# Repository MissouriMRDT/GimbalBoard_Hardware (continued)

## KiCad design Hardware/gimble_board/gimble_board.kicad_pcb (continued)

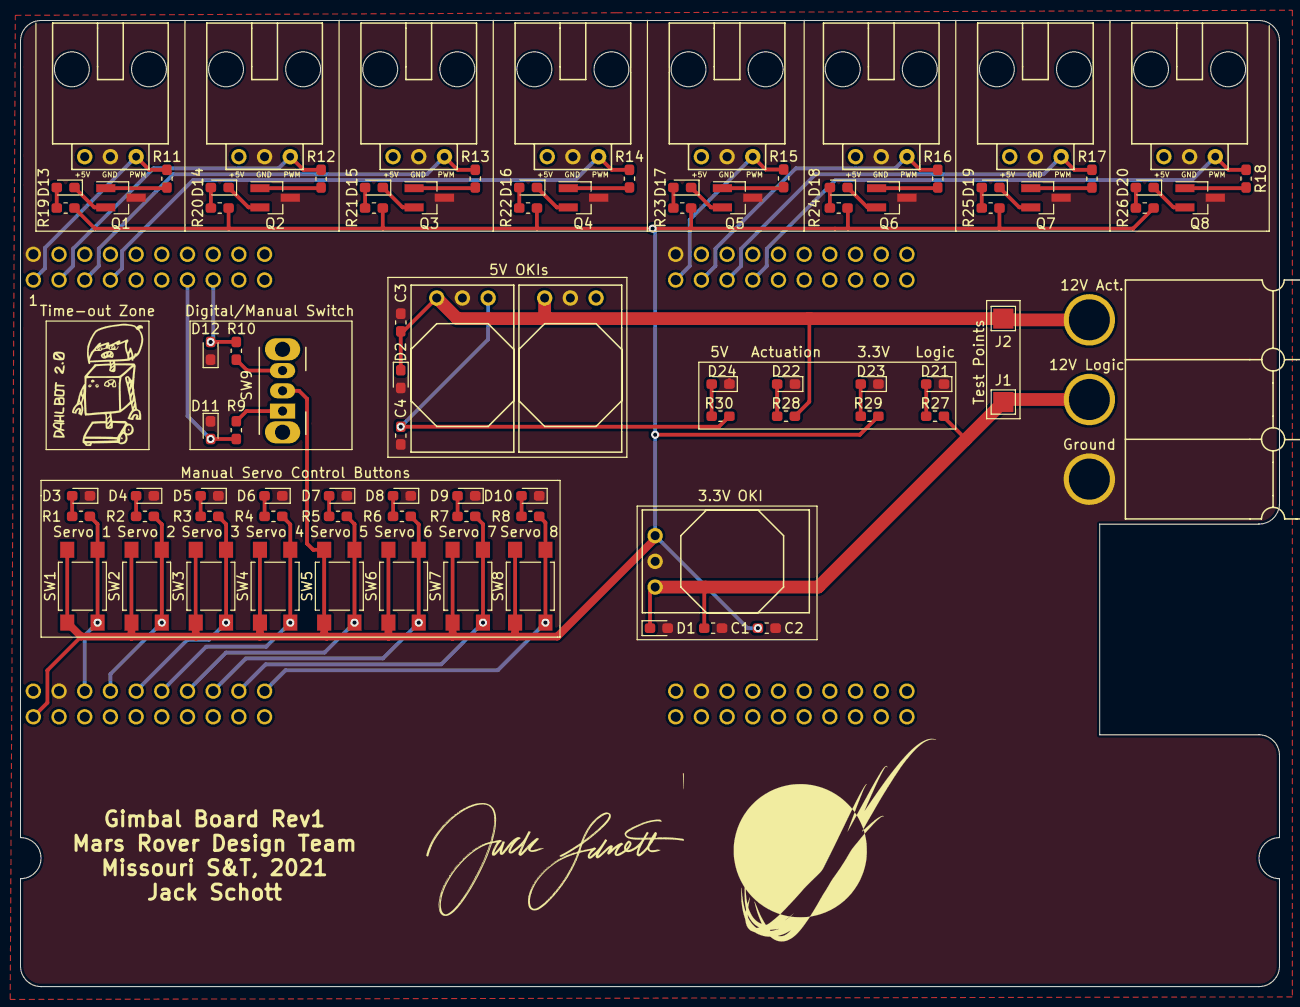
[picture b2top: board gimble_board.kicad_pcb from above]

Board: 2 copper layers, 124.5 x 95.5 mm, 90 parts (0 on the bottom side), 61 nets.

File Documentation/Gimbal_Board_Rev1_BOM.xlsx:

Id | Designator | Package | Quantity | Designation | Item Name | Part Number | Vendor | Cost Per Item | Cost | URL | Comments | Quantity
1 | U1 | TM4C129E_Launchpad_FULL_THT_BOTTOM | 4 | TM4C129E_Launchpad | 20 Position Header Connector Through Hole | S6106-ND | DigiKey | 1.26 |  | https://www.digikey.com/product-detail/en/sullins-connector-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 |  | 4 |  | Total Cost
2 | R6,R5,R26,R25,R24,R23,R22,R21,R20,R19,R18,R17,R1,R2,R3,R4,R28,R7,R8 | R_0603_1608Metric_Pad1.05x0.95mm_HandSolder | 19 | 330 | 330 Ohms ±1% 0.1W, 1/10W Chip Resistor 0603 | P330HCT-ND | DigiKey | 0.1 |  | https://www.digikey.com/product-detail/en/panasonic-electron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 |  | 19 |  | 14.103
3 | R14,R27,R9,R10,R11,R12,R13,R15,R16 | R_0603_1608Metric_Pad1.05x0.95mm_HandSolder | 9 | 500 | SMD Chip Resistor, 0603 [1608 Metric], 510 ohm, CRCW e3 Series, 75 V, Thick Fil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 | 59M6823 | Newark | 0.004 |  | https://www.newark.com/vishay/crcw0603510rjnea/res-thick-fil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 |  | 9
4 | Q6,Q5,Q8,Q7,Q4,Q3,Q2,Q1 | SOT-23_Handsoldering | 8 | Q_NMOS_GDS | N-Channel 60V 310mA (Ta) 370mW (Ta) Surface Mount SOT-23 | DMN65D8L-7DICT-ND | DigiKey | 0.17 |  | https://www.digikey.com/product-detail/en/diodes-incorporate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 |  | 8
5 | D6,D18,D17,D16,D15,D14,D13,D12,D11,D10,D9,D1,D2,D3,D4,D5,D7,D8 | D_0603_1608Metric_Pad1.05x0.95mm_HandSolder | 18 | LED | LED, QuasarBrite, Orange, SMD, 0603, 20 mA, 2 V, 610 nm | 28M9279 | Newark | 0.117 |  | https://www.newark.com/lumex/sml-lx0603sow-tr/led-orange-0-8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 |  | 18
6 | Conn6,Conn1,Conn2,Conn3,Conn4,Conn5,Conn7,Conn8 | MOLEX_SL_03_Horizontal | 8 | Molex_SL_03 | Connector Header Through Hole, Right Angle 3 position 0.100" (2.54mm) | WM4901-ND | DigiKey | 1.02 |  | https://www.digikey.com/products/en?keywords=WM4901-ND |  | 8
7 | SW10 | SW_CuK_OS102011MA1QN1_SPDT_Angled | 1 | SW_SPDT | Slide Switch SPDT Through Hole, Right Angle | CKN9559-ND | DigiKey | 0.38 |  | https://www.digikey.com/products/en?keywords=CKN9559-ND |  | 1
8 | SW9,SW8,SW7,SW6,SW5,SW4,SW3,SW2,SW1 | SW_SPST_TL3305A | 9 | SW_Push | Tactile Switch SPST-NO Top Actuated Surface Mount | EG5350CT-ND | DigiKey | 0.2 |  | https://www.digikey.com/product-detail/en/e-switch/TL3305AF1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 |  | 9
9 | C6,C5,C7 | CP_Radial_D8.0mm_P3.50mm | 3 | 470u | CAP ALUM 470UF 20% 16V RADIAL | 1189-1859-ND | DigiKey | 0.4 |  | https://www.digikey.com/product-detail/en/rubycon/16ZLH470ME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 |  | 3
10 | C1,C2 | C_0603_1608Metric_Pad1.05x0.95mm_HandSolder | 2 | 10 uF | CAP CER 10UF 16V X5R 0603 | 490-12736-1-ND | DigiKey | 0.39 |  | https://www.digikey.com/product-detail/en/murata-electronics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 |  | 2
11 | C3,C4 | C_0603_1608Metric_Pad1.05x0.95mm_HandSolder | 2 | 10uF | CAP CER 10UF 16V X5R 0603 | 490-12736-1-ND | DigiKey | 0.39 |  | https://www.digikey.com/product-detail/en/murata-electronics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 |  | 2
12 | D20 | D_0603_1608Metric_Pad1.05x0.95mm_HandSolder | 1 | 3V_LED | LED, QuasarBrite, Green, SMD, 0603, 20 mA, 2.2 V, 565 nm | 75K1440 | Newark | 0.243 |  | https://www.newark.com/lumex/sml-lx0603gw-tr/led-green-0-8mm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 |  | 1
13 | D19 | D_0603_1608Metric_Pad1.05x0.95mm_HandSolder | 1 | 5V_Act_LED | LED, QuasarBrite, Green, SMD, 0603, 20 mA, 2.2 V, 565 nm | 75K1440 | Newark | 0.243 |  | https://www.newark.com/lumex/sml-lx0603gw-tr/led-green-0-8mm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 |  | 1
14 | U2 | OkI_Horizontal_3V3 | 1 | OKI | Linear Regulator Replacement DC DC Converter 1 Output 3.3V 1.5A 7V - 36V Input | 811-3014-ND | DigiKey | 4.3 |  | https://www.digikey.com/product-detail/en/murata-power-solut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 |  | 1
15 | U3 | OKI_Horizontal_5V | 1 | OKI | Linear Regulator Replacement DC DC Converter 1 Output 5V 1.5A 7V - 36V Input | 811-2692-ND | DigiKey | 4.3 |  | https://www.digikey.com/product-detail/en/murata-power-solut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 |  | 1
16 | Conn9 | Anderson_3_Horizontal_Side_by_Side | 1 | AndersonPP |  |  |  |  |  |  |  | 1
17 | D21 | D_0603_1608Metric_Pad1.05x0.95mm_HandSolder | 1 | 12V_Log_LED | LED, QuasarBrite, Green, SMD, 0603, 20 mA, 2.2 V, 565 nm | 75K1440 | Newark | 0.243 |  | https://www.newark.com/lumex/sml-lx0603gw-tr/led-green-0-8mm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 |  | 1
18 | D22 | D_0603_1608Metric_Pad1.05x0.95mm_HandSolder | 1 | 12V_Act_LED | LED, QuasarBrite, Green, SMD, 0603, 20 mA, 2.2 V, 565 nm | 75K1440 | Newark | 0.243 |  | https://www.newark.com/lumex/sml-lx0603gw-tr/led-green-0-8mm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 |  | 1
19 | R29,R30 | R_0603_1608Metric_Pad1.05x0.95mm_HandSolder | 2 | 1000 | 1 kOhms ±5% 0.25W, 1/4W Chip Resistor 0603 (1608 Metric) Automotive AEC-Q200, P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 | RHM1.0KDCT-ND | DigiKey | 0.1 |  | https://www.digikey.com/product-detail/en/rohm-semiconductor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 |  | 2

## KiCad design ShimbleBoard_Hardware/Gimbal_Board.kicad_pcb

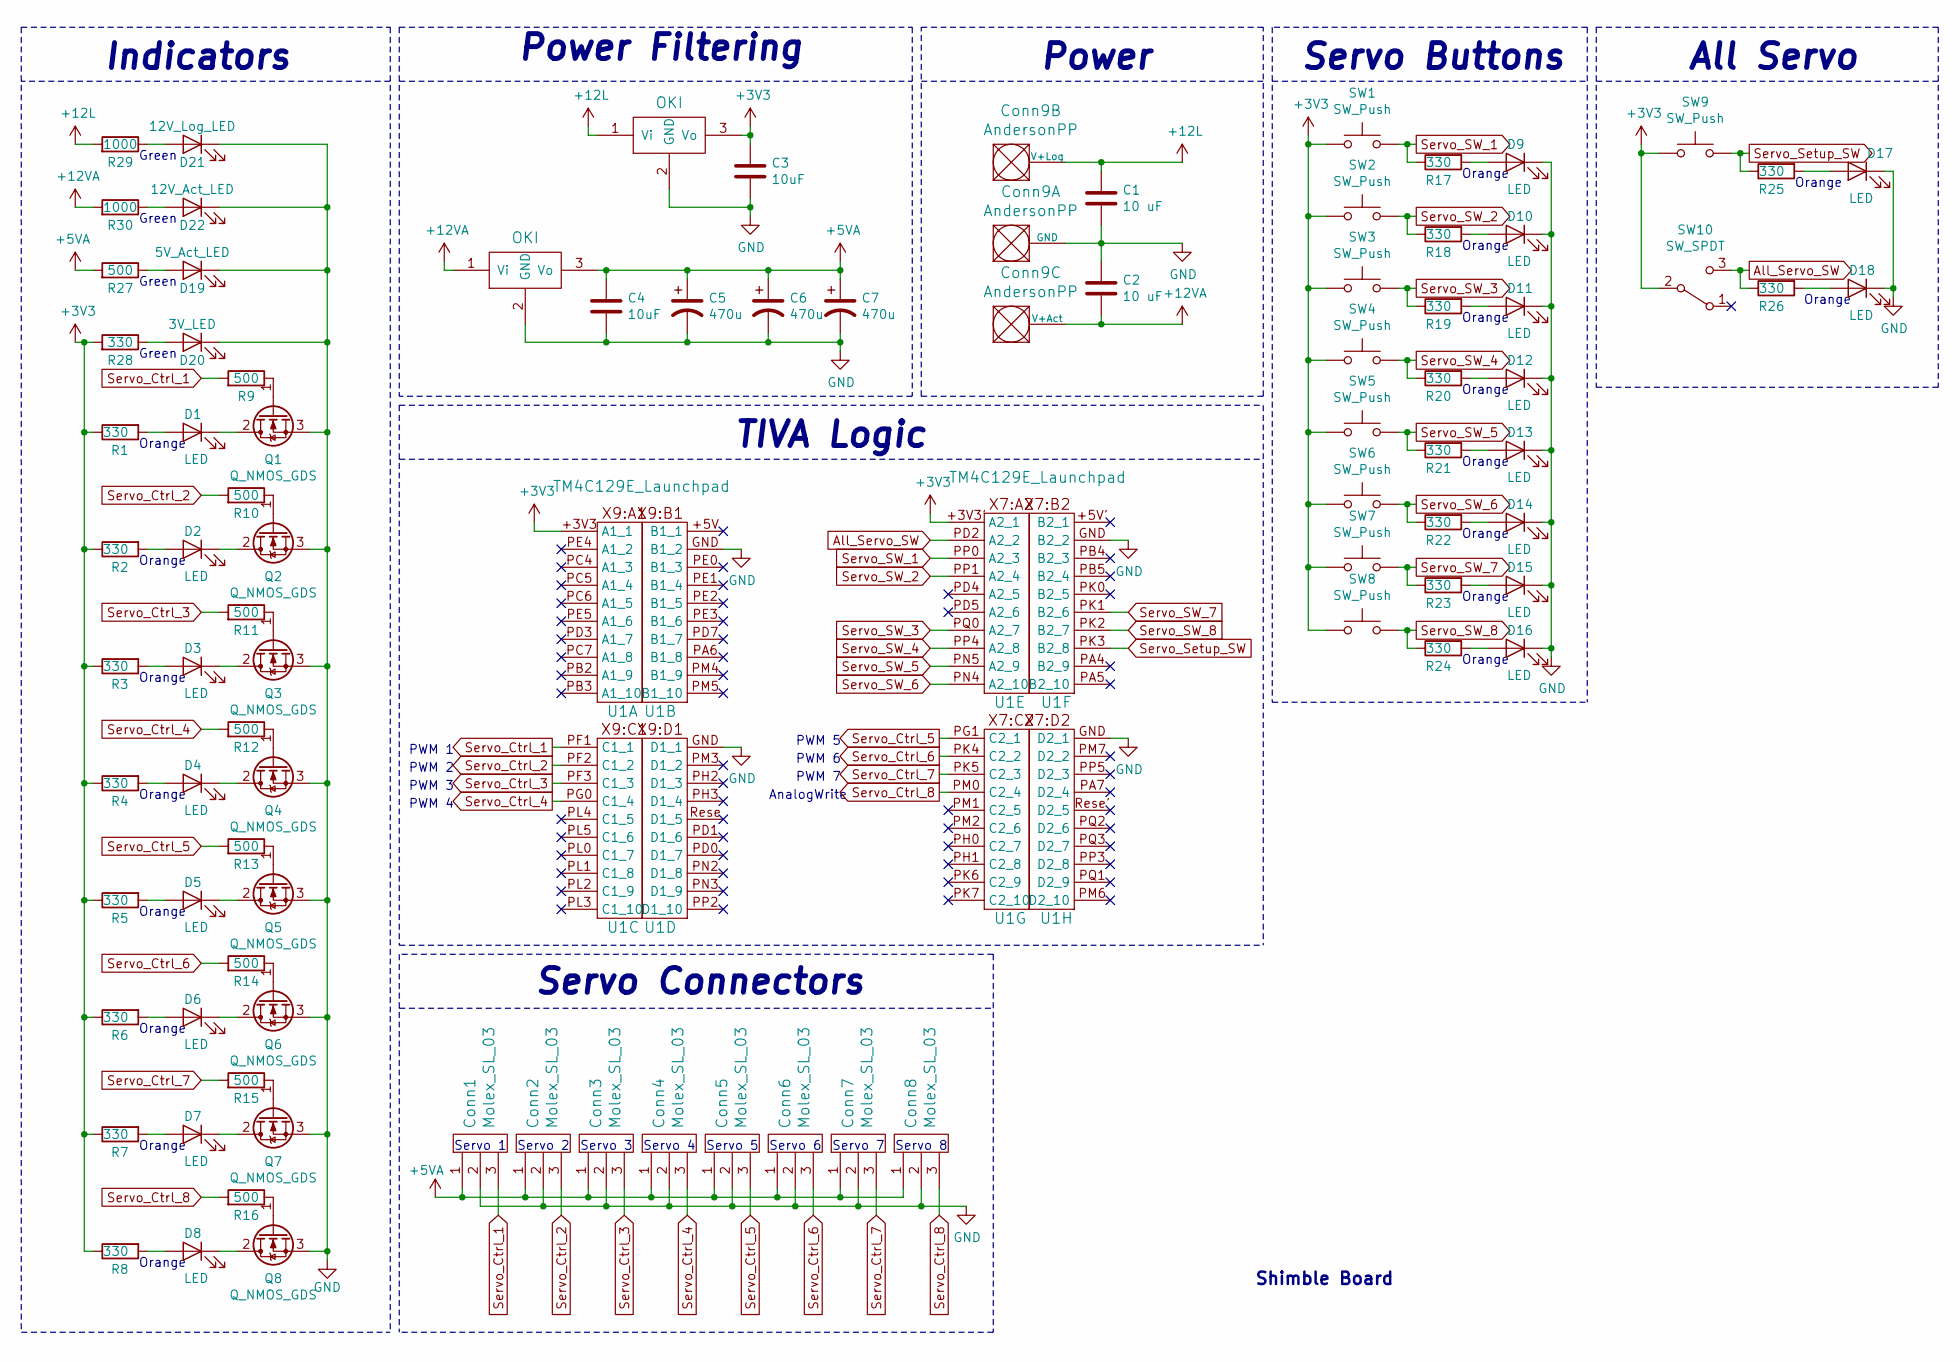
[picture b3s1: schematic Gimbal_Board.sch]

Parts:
C1, C2: 10 uF; C_0603_1608Metric_Pad1.05x0.95mm_HandSolder
C3, C4: 10uF; C_0603_1608Metric_Pad1.05x0.95mm_HandSolder
C5, C6, C7: 470u; CP_Radial_D8.0mm_P3.50mm
Conn1, Conn2, Conn3, Conn4, Conn5, Conn6, Conn7, Conn8: Molex_SL_03; MOLEX_SL_03_Horizontal
Conn9: AndersonPP; Anderson_3_Horizontal_Side_by_Side
D1, D2, D3, D4, D5, D6, D7, D8, D9, D10, D11, D12, D13, D14, D15, D16, D17, D18: LED; D_0603_1608Metric_Pad1.05x0.95mm_HandSolder
D19: 5V_Act_LED; D_0603_1608Metric_Pad1.05x0.95mm_HandSolder
D20: 3V_LED; D_0603_1608Metric_Pad1.05x0.95mm_HandSolder
D21: 12V_Log_LED; D_0603_1608Metric_Pad1.05x0.95mm_HandSolder
D22: 12V_Act_LED; D_0603_1608Metric_Pad1.05x0.95mm_HandSolder
Q1, Q2, Q3, Q4, Q5, Q6, Q7, Q8: Q_NMOS_GDS; SOT-23_Handsoldering
R1, R2, R3, R4, R5, R6, R7, R8, R17, R18, R19, R20, R21, R22, R23, R24, R25, R26, R28: 330; R_0603_1608Metric_Pad1.05x0.95mm_HandSolder
R9, R10, R11, R12, R13, R14, R15, R16, R27: 500; R_0603_1608Metric_Pad1.05x0.95mm_HandSolder
R29, R30: 1000; R_0603_1608Metric_Pad1.05x0.95mm_HandSolder
SW1, SW2, SW3, SW4, SW5, SW6, SW7, SW8, SW9: SW_Push; SW_SPST_TL3305A
SW10: SW_SPDT; SW_CuK_OS102011MA1QN1_SPDT_Angled
U1: TM4C129E_Launchpad; TM4C129E_Launchpad_FULL_THT_BOTTOM
U2, U3: OKI; OKI_Horizontal

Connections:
+3V3: C3.1, R1.1, R2.1, R3.1, R4.1, R5.1, R6.1, R7.1, R8.1, R28.2, SW1.1, SW2.1, SW3.1, SW4.1, SW5.1, SW6.1, SW7.1, SW8.1, SW9.1, SW10.2 (B), U1.+3V3 (A1_1), U1.+3V3' (A2_1), U2.3 (Vo)
+5VA: C4.1, C5.1, C6.1, C7.1, Conn1.1, Conn2.1, Conn3.1, Conn4.1, Conn5.1, Conn6.1, Conn7.1, Conn8.1, R27.2, U3.3 (Vo)
+12L: C1.1, Conn9.2 (V+Log), R29.2, U2.1 (Vi)
+12VA: C2.2, Conn9.3 (V+Act), R30.2, U3.1 (Vi)
All_Servo_SW: R26.1, SW10.3 (C), U1.PD2 (A2_2)
GND: C1.2, C2.1, C3.2, C4.2, C5.2, C6.2, C7.2, Conn1.2, Conn2.2, Conn3.2, Conn4.2, Conn5.2, Conn6.2, Conn7.2, Conn8.2, Conn9.1 (GND), D9.1 (K), D10.1 (K), D11.1 (K), D12.1 (K), D13.1 (K), D14.1 (K), D15.1 (K), D16.1 (K), D17.1 (K), D18.1 (K), D19.1 (K), D20.1 (K), D21.1 (K), D22.1 (K), Q1.3 (S), Q2.3 (S), Q3.3 (S), Q4.3 (S), Q5.3 (S), Q6.3 (S), Q7.3 (S), Q8.3 (S), U1.GND (B1_2), U2.2 (GND), U3.2 (GND)
unnamed: D1.1 (K), Q1.2 (D)
unnamed: D1.2 (A), R1.2
unnamed: D2.1 (K), Q2.2 (D)
unnamed: D2.2 (A), R2.2
unnamed: D3.1 (K), Q3.2 (D)
unnamed: D3.2 (A), R3.2
unnamed: D4.1 (K), Q4.2 (D)
unnamed: D4.2 (A), R4.2
unnamed: D5.1 (K), Q5.2 (D)
unnamed: D5.2 (A), R5.2
unnamed: D6.1 (K), Q6.2 (D)
unnamed: D6.2 (A), R6.2
unnamed: D7.1 (K), Q7.2 (D)
unnamed: D7.2 (A), R7.2
unnamed: D8.1 (K), Q8.2 (D)
unnamed: D8.2 (A), R8.2
unnamed: D9.2 (A), R17.2
unnamed: D10.2 (A), R18.2
unnamed: D11.2 (A), R19.2
unnamed: D12.2 (A), R20.2
unnamed: D13.2 (A), R21.2
unnamed: D14.2 (A), R22.2
unnamed: D15.2 (A), R23.2
unnamed: D16.2 (A), R24.2
unnamed: D17.2 (A), R25.2
unnamed: D18.2 (A), R26.2
unnamed: D19.2 (A), R27.1
unnamed: D20.2 (A), R28.1
unnamed: D21.2 (A), R29.1
unnamed: D22.2 (A), R30.1
unnamed: Q1.1 (G), R9.1
unnamed: Q2.1 (G), R10.1
unnamed: Q3.1 (G), R11.1
unnamed: Q4.1 (G), R12.1
unnamed: Q5.1 (G), R13.1
unnamed: Q6.1 (G), R14.1
unnamed: Q7.1 (G), R15.1
unnamed: Q8.1 (G), R16.1
Servo_Ctrl_1: Conn1.3, R9.2, U1.PF1 (C1_1)
Servo_Ctrl_2: Conn2.3, R10.2, U1.PF2 (C1_2)
Servo_Ctrl_3: Conn3.3, R11.2, U1.PF3 (C1_3)
Servo_Ctrl_4: Conn4.3, R12.2, U1.PG0 (C1_4)
Servo_Ctrl_5: Conn5.3, R13.2, U1.PG1 (C2_1)
Servo_Ctrl_6: Conn6.3, R14.2, U1.PK4 (C2_2)
Servo_Ctrl_7: Conn7.3, R15.2, U1.PK5 (C2_3)
Servo_Ctrl_8: Conn8.3, R16.2, U1.PM0 (C2_4)
Servo_SW_1: R17.1, SW1.2, U1.PP0 (A2_3)
Servo_SW_2: R18.1, SW2.2, U1.PP1 (A2_4)
Servo_SW_3: R19.1, SW3.2, U1.PQ0 (A2_7)
Servo_SW_4: R20.1, SW4.2, U1.PP4 (A2_8)
Servo_SW_5: R21.1, SW5.2, U1.PN5 (A2_9)
Servo_SW_6: R22.1, SW6.2, U1.PN4 (A2_10)
Servo_SW_7: R23.1, SW7.2, U1.PK1 (B2_6)
Servo_SW_8: R24.1, SW8.2, U1.PK2 (B2_7)
Servo_Setup_SW: R25.1, SW9.2, U1.PK3 (B2_8)

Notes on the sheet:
Shimble Board
Orange
Green
Indicators
Power
Power Filtering
PWM 7
PWM 6
PWM 5
AnalogWrite
TIVA Logic
PWM 1
PWM 3
PWM 4
PWM 2
Servo 1
Servo 2
Servo 3
Servo 4
Servo 5
Servo 6
Servo 7
Servo 8
Servo Connectors
Servo Buttons
All Servo

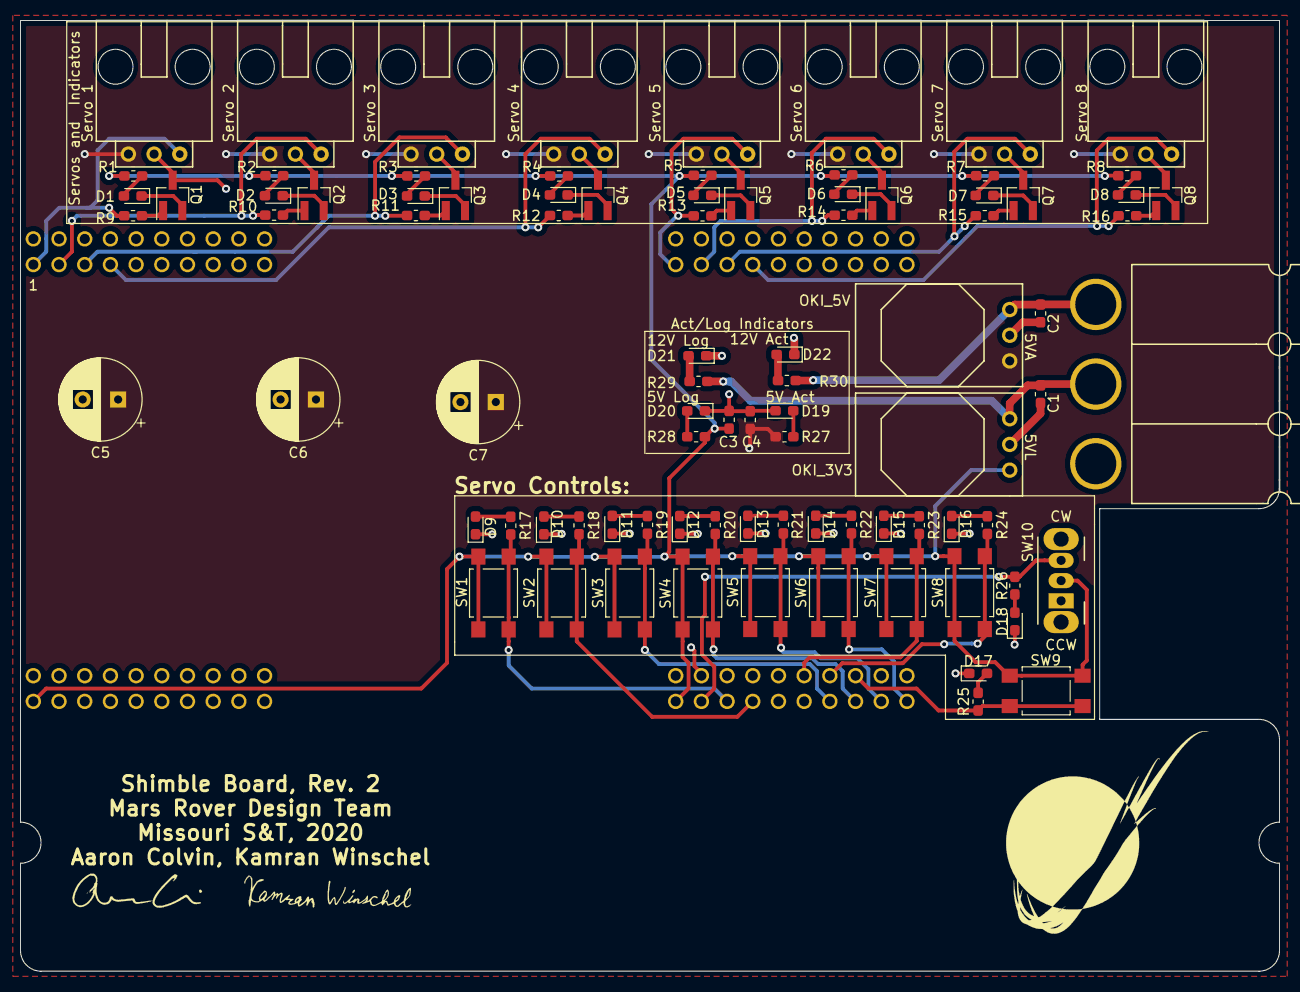
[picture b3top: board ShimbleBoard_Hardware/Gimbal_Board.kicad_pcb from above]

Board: 2 copper layers, 124.5 x 94.0 mm, 89 parts (0 on the bottom side), 61 nets.

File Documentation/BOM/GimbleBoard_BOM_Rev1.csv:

"Id","Designator","Package","Quantity","Designation","Supplier and ref",
1,"G***","2_Dahlbot_2.0",1,"LOGO",,,
2,"G***","0_MRDT_Logo_20mm",1,"LOGO",,,
3,"G***","z_sig_Jack_Schott_15.2mmx27mm",1,"LOGO",,,
4,"U3","TM4C129E_Launchpad_FULL_THT_BOTTOM",1,"TM4C129E_Launchpad",,,
5,"D9,D3,D4,D5,D6,D7,D8,D10,D11,D12,D13,D14,D15,D16,D17,D18,D19,D20,D21,D22,D23,D24","LED_0603_1608Metric_Pad1.05x0.95mm_HandSolder",22,"LED",,,
6,"D1,D2","LED_0603_1608Metric_Pad1.05x0.95mm_HandSolder",2,"D_Zener",,,
7,"J1,J2","TestPoint_Pad_2.0x2.0mm",2,"Test_Point",,,
8,"Q1,Q2,Q3,Q4,Q5,Q6,Q7,Q8","SOT-23_Handsoldering",8,"Q_NMOS_GDS",,,
9,"SW1,SW2,SW3,SW4,SW5,SW6,SW7,SW8","SW_SPST_TL3305A",8,"SW_Push",,,
10,"SW9","SW_CuK_OS102011MA1QN1_SPDT_Angled",1,"SW_SPDT",,,
11,"Conn1","Anderson_3_Horizontal_Side_by_Side",1,"AndersonPP",,,
12,"Conn2,Conn3,Conn4,Conn5,Conn6,Conn7,Conn8,Conn9","MOLEX_SL_03_Horizontal",8,"Molex_SL_03",,,
13,"R1,R2,R3,R4,R5,R6,R7,R8,R9,R10,R19,R20,R21,R22,R23,R24,R25,R26,R29,R30","R_0603_1608Metric_Pad1.05x0.95mm_HandSolder",20,"330",,,
14,"R11,R12,R13,R14,R15,R16,R17,R18","R_0603_1608Metric_Pad1.05x0.95mm_HandSolder",8,"500",,,
15,"C1,C2,C3,C4","C_0603_1608Metric_Pad1.05x0.95mm_HandSolder",4,"10uF",,,
16,"U1,U2,U4","OKI_Horizontal",3,"OKI",,,
17,"R27,R28","R_0603_1608Metric_Pad1.05x0.95mm_HandSolder",2,"1000",,,

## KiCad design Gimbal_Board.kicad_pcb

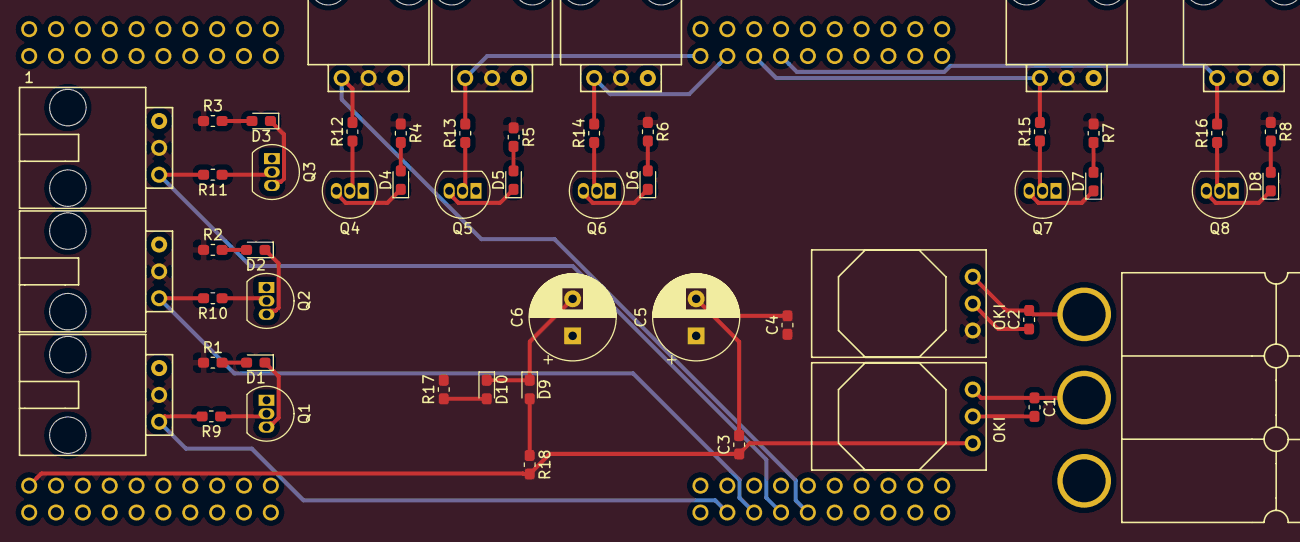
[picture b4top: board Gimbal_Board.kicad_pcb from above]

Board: 2 copper layers, 54 parts (0 on the bottom side), 39 nets.

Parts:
C1, C2: 10 uF; C_0603_1608Metric_Pad1.05x0.95mm_HandSolder
C3, C4: 10uF; C_0603_1608Metric_Pad1.05x0.95mm_HandSolder
C5, C6: 470u; CP_Radial_D8.0mm_P3.50mm
Conn1, Conn2, Conn3, Conn4, Conn5, Conn6, Conn7, Conn8: Molex_SL_03; MOLEX_SL_03_Horizontal
Conn9: AndersonPP; Anderson_3_Horizontal_Side_by_Side
D1, D2, D3, D4, D5, D6, D7, D8: LED; D_0603_1608Metric_Pad1.05x0.95mm_HandSolder
D9: 5V_Log_LED; D_0603_1608Metric_Pad1.05x0.95mm_HandSolder
D10: 5V_Act_LED; D_0603_1608Metric_Pad1.05x0.95mm_HandSolder
Q1, Q2, Q3, Q4, Q5, Q6, Q7, Q8: 2N3904; TO-92_Inline
R1, R2, R3, R4, R5, R6, R7, R8, R9, R10, R11, R12, R13, R14, R15, R16: 100; R_0603_1608Metric_Pad1.05x0.95mm_HandSolder
R17, R18: 1000; R_0603_1608Metric_Pad1.05x0.95mm_HandSolder
U1: TM4C129E_Launchpad; TM4C129E_Launchpad_FULL_THT_BOTTOM
U2, U3: OKI; OKI_Horizontal

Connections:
+5VA: C4.1, C5.1, C6.1, Conn1.2, Conn2.2, Conn3.2, Conn4.2, Conn5.2, Conn6.2, Conn7.2, Conn8.2, R1.1, R2.1, R3.1, R4.1, R5.1, R6.1, R7.1, R8.1, R17.2, U3.3
+5VL: C3.1, R18.2, U1.+5V', U2.3
+12L: C1.1, Conn9.2, U2.1
+12VA: C2.2, Conn9.3, U3.1
GND: C1.2, C2.1, C3.2, C4.2, C5.2, C6.2, Conn1.3, Conn2.3, Conn3.3, Conn4.3, Conn5.3, Conn6.3, Conn7.3, Conn8.3, Conn9.1, D9.1, D10.1, Q1.1, Q2.1, Q3.1, Q4.1, Q5.1, Q6.1, Q7.1, Q8.1, U1.GND, U2.2, U3.2
unnamed: D1.1, Q1.3
unnamed: D1.2, R1.2
unnamed: D2.1, Q2.3
unnamed: D2.2, R2.2
unnamed: D3.1, Q3.3
unnamed: D3.2, R3.2
unnamed: D4.1, Q4.3
unnamed: D4.2, R4.2
unnamed: D5.1, Q5.3
unnamed: D5.2, R5.2
unnamed: D6.1, Q6.3
unnamed: D6.2, R6.2
unnamed: D7.1, Q7.3
unnamed: D7.2, R7.2
unnamed: D8.1, Q8.3
unnamed: D8.2, R8.2
unnamed: D9.2, R18.1
unnamed: D10.2, R17.1
unnamed: Q1.2, R9.1
unnamed: Q2.2, R10.1
unnamed: Q3.2, R11.1
unnamed: Q4.2, R12.1
unnamed: Q5.2, R13.1
unnamed: Q6.2, R14.1
unnamed: Q7.2, R15.1
unnamed: Q8.2, R16.1
Servo_Ctrl_1: Conn1.1, R9.2, U1.PD2
Servo_Ctrl_2: Conn2.1, R10.2, U1.PP0
Servo_Ctrl_3: Conn3.1, R11.2, U1.PP1
Servo_Ctrl_4: Conn4.1, R12.2, U1.PD4
Servo_Ctrl_5: Conn5.1, R13.2, U1.PG1
Servo_Ctrl_6: Conn6.1, R14.2, U1.PK4
Servo_Ctrl_7: Conn7.1, R15.2, U1.PK5
Servo_Ctrl_8: Conn8.1, R16.2, U1.PM0

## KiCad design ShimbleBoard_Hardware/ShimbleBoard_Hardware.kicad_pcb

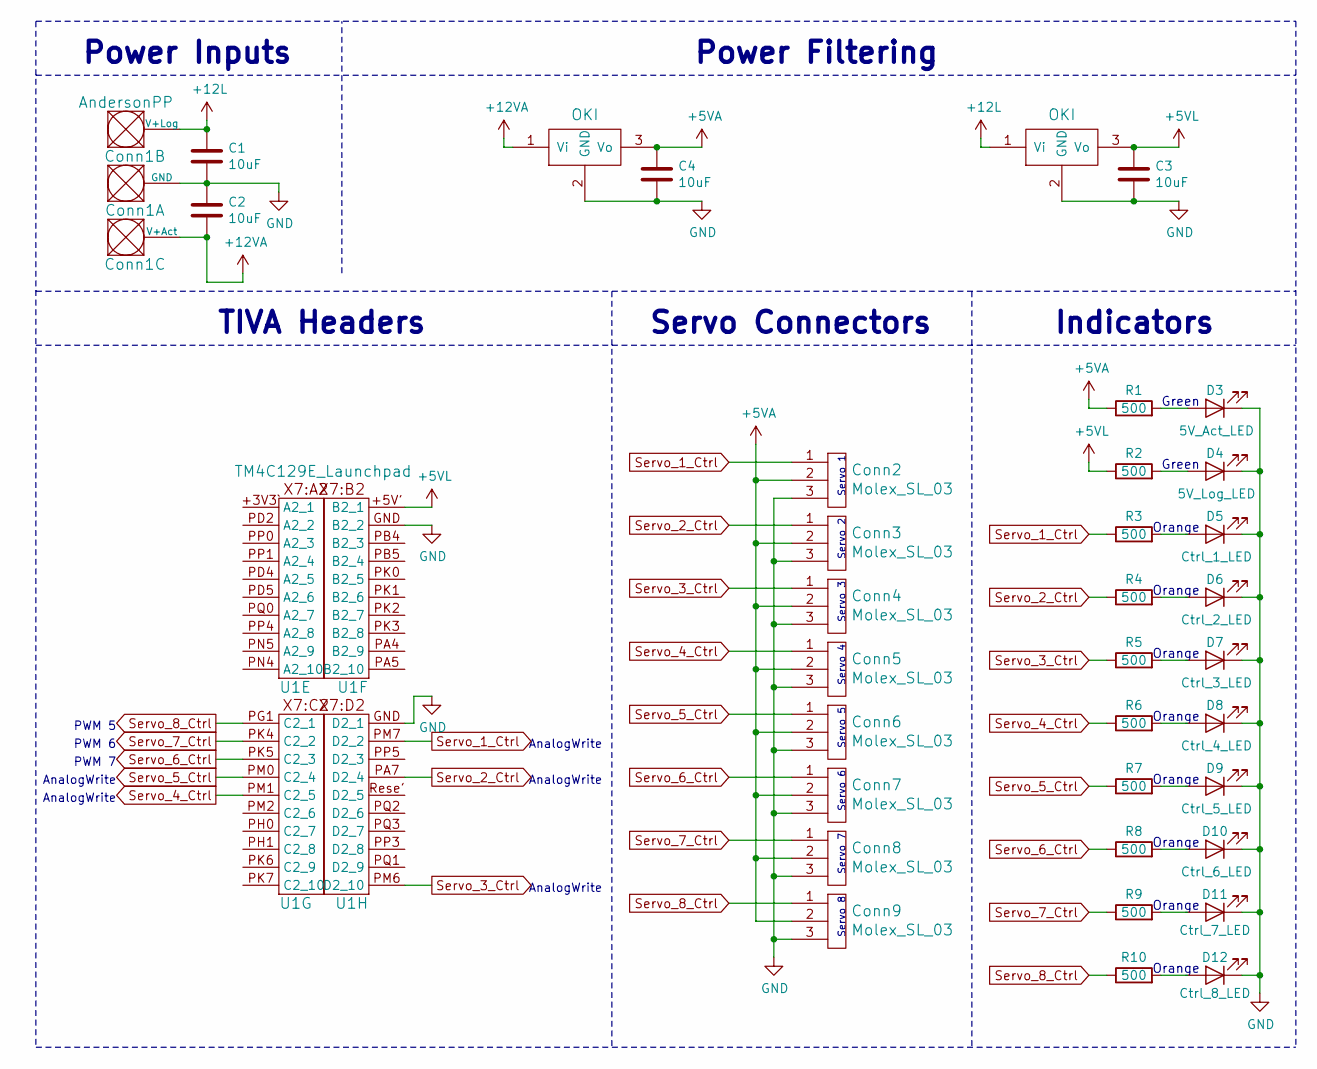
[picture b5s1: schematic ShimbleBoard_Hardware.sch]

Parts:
C1, C2, C3, C4: 10uF; C_0603_1608Metric_Pad1.05x0.95mm_HandSolder
Conn1: AndersonPP; Anderson_3_Horizontal_Side_by_Side
Conn2, Conn3, Conn4, Conn5, Conn6, Conn7, Conn8, Conn9: Molex_SL_03; MOLEX_SL_03_Horizontal
D3: 5V_Act_LED; D_0603_1608Metric_Pad1.05x0.95mm_HandSolder
D4: 5V_Log_LED; D_0603_1608Metric_Pad1.05x0.95mm_HandSolder
D5: Ctrl_1_LED; D_0603_1608Metric_Pad1.05x0.95mm_HandSolder
D6: Ctrl_2_LED; D_0603_1608Metric_Pad1.05x0.95mm_HandSolder
D7: Ctrl_3_LED; D_0603_1608Metric_Pad1.05x0.95mm_HandSolder
D8: Ctrl_4_LED; D_0603_1608Metric_Pad1.05x0.95mm_HandSolder
D9: Ctrl_5_LED; D_0603_1608Metric_Pad1.05x0.95mm_HandSolder
D10: Ctrl_6_LED; D_0603_1608Metric_Pad1.05x0.95mm_HandSolder
D11: Ctrl_7_LED; D_0603_1608Metric_Pad1.05x0.95mm_HandSolder
D12: Ctrl_8_LED; D_0603_1608Metric_Pad1.05x0.95mm_HandSolder
R1, R2, R3, R4, R5, R6, R7, R8, R9, R10: 500; R_0603_1608Metric_Pad1.05x0.95mm_HandSolder
U1: TM4C129E_Launchpad; TM4C129E_Launchpad_X7_THT_BOTTOM
U2, U3: OKI; OKI_Horizontal

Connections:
+5VA: C4.1, Conn2.2, Conn3.2, Conn4.2, Conn5.2, Conn6.2, Conn7.2, Conn8.2, Conn9.2, R1.1, U2.3 (Vo)
+5VL: C3.1, R2.1, U1.+5V' (B2_1), U3.3 (Vo)
+12L: C1.1, Conn1.2 (V+Log), U3.1 (Vi)
+12VA: C2.2, Conn1.3 (V+Act), U2.1 (Vi)
GND: C1.2, C2.1, C3.2, C4.2, Conn1.1 (GND), Conn2.3, Conn3.3, Conn4.3, Conn5.3, Conn6.3, Conn7.3, Conn8.3, Conn9.3, D3.1 (K), D4.1 (K), D5.1 (K), D6.1 (K), D7.1 (K), D8.1 (K), D9.1 (K), D10.1 (K), D11.1 (K), D12.1 (K), U1.GND (B1_2), U2.2 (GND), U3.2 (GND)
unnamed: D3.2 (A), R1.2
unnamed: D4.2 (A), R2.2
unnamed: D5.2 (A), R3.2
unnamed: D6.2 (A), R4.2
unnamed: D7.2 (A), R5.2
unnamed: D8.2 (A), R6.2
unnamed: D9.2 (A), R7.2
unnamed: D10.2 (A), R8.2
unnamed: D11.2 (A), R9.2
unnamed: D12.2 (A), R10.2
Servo_1_Ctrl: Conn2.1, R3.1, U1.PM7 (D2_2)
Servo_2_Ctrl: Conn3.1, R4.1, U1.PA7 (D2_4)
Servo_3_Ctrl: Conn4.1, R5.1, U1.PM6 (D2_10)
Servo_4_Ctrl: Conn5.1, R6.1, U1.PM1 (C2_5)
Servo_5_Ctrl: Conn6.1, R7.1, U1.PM0 (C2_4)
Servo_6_Ctrl: Conn7.1, R8.1, U1.PK5 (C2_3)
Servo_7_Ctrl: Conn8.1, R9.1, U1.PK4 (C2_2)
Servo_8_Ctrl: Conn9.1, R10.1, U1.PG1 (C2_1)

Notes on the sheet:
TIVA Headers
Servo Connectors
Power Filtering
Servo 1
Servo 2
Servo 3
Servo 4
Servo 5
Servo 6
Servo 7
Servo 8
Power Inputs
Indicators
PWM 5
PWM 6
PWM 7
AnalogWrite
Green
Orange

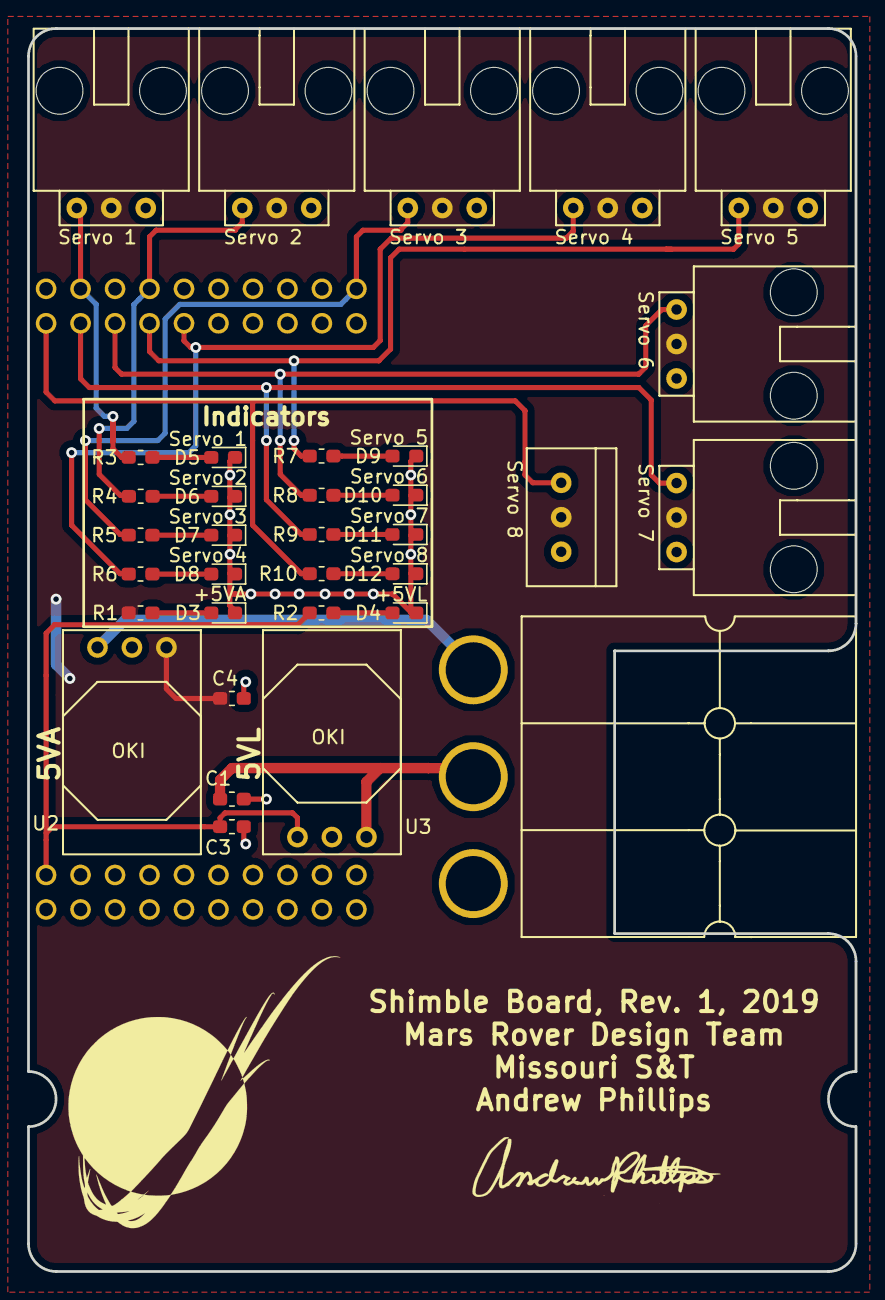
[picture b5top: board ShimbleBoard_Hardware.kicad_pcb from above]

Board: 2 copper layers, 61.0 x 91.6 mm, 36 parts (1 on the bottom side), 23 nets.

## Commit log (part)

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2018-10-22 Beginning work
2018-10-22 Schematic Finished Draft
2018-10-22 Preliminary Board Layout
2018-10-25 Block Diagram
2018-10-26 Txt Files and Reorganized Board
2018-10-26 Removed Servo 8 & Increased Power Track Width
2018-10-26 .gitignore added
2018-10-27 fixed board connectors
2018-10-27 Fixed Minor Issues
2018-11-11 Post PDR
2018-11-16 Board Review
2018-11-17 Post Board Review 1
2018-11-17 Revised Schematic
2018-11-26 Work hours 2018-11-17
2018-11-29 Preliminary traces completed & Various review changes
2018-12-14 BOM and Redesigned AP1509 Area
2018-12-14 PRR Take 1
2018-12-15 PRR Take 2: OKI Boogaloo
2018-12-16 Finalized board and made adjustments
2018-12-16 Finished PRR: Gerbs
2018-12-31 2019 Rev 1 Merge
    Merge conflicts in pull request
2019-02-15 Updated Rev2 Libraries
2019-03-05 Fixed Servo Wiring
2019-03-05 Added caps and silkscreen
2019-03-05 Rev2 Gerbs Created
2019-03-05 Updated BOM
2019-09-28 Day 1
2019-09-30 Schematic additions
    Status of each section is located at the top of the schematic. Added the much of the designs from last year. Used the updated indicator design (needs to be looked over). Tiva Logic needs to be looked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
2019-09-30 6 Servo Changes
    Changed to be 6 servos. Pins should be looked over. (Old Indicators should be deleted if no one needs it for reference on this file).
2019-10-02 Added some notes
2019-10-02 Need more servos n such
2019-10-02 Changed to 8 servo (again)
    Added two more servo inputs and relabeled some components.
2019-10-08 Footprints Assigned, Netlist Generated, and PCB layout started
    As it is in the title. Connecters and anderson placed on board. Servo pins changed.
2019-10-08 PMW to PWM
2019-10-09 PCB first layout complete
    Finished first PCB layout and ratsnest.
2019-10-09 Minor Schematic changes
    Labeling and numbering for resistors
2019-10-09 Cleaned up
2019-10-09 test...
2019-10-09 moved
2019-10-09 Cleaning
2019-10-09 Cleaned
2019-10-09 Missed gnd
2019-10-09 Re-Oriented stuff
2019-10-09 Added names
2019-10-10 Minor Schematic changes
    Moved some schematic sections around.
2019-10-11 Noice
2019-10-11 Still need Sig's
2019-10-11 Silkscreens Added
    Signitures and logo was added.
    Schematic cleaned up a little.
2019-10-12 Added signature file
2019-10-12 Added sig
2019-10-12 2020
2019-10-12 something
2019-10-12 Pins Fixed
    PCB layout is also a bit cleaner
2019-10-12 Sigs Re-added
    Signitures and Logo added back
2019-10-12 Cleaned up some wires
    Back copper wires of the leftmost connecters.
2019-10-12 Changed a wire
    A wire was on the wrong track, remade it to be 15 mils
2019-10-27 BJT changes
    BJT changed to surface mount
    Minor re-wiring
    Ground & +5VA plains changed to solid
2019-10-27 Resistor Changes
    Resistors changed to 500 standard
2019-10-27 Minor text change
    AnalogWrite
2019-10-31 Major Overhaull
    BJTs replaced by N-MOSFET
    Buttons & switch added
    PCB layout worked on (still not complete)
2019-11-01 PCB placement (not finished
    PCB component placement and wiring
    Still needs a lot more work, button pins need to be determined
2019-11-10 Layout changes
    Moved some stuff
2019-11-15 Cleaned some stuff
2019-11-15 Moved some buttons
2019-11-15 All Connected I Believe
2019-11-15 Moved Labels
2019-11-16 Added border that needs fixing
2019-11-16 Fixed stuff
2019-11-16 idk what I changed but i changed something apparently
2019-11-16 Clean and spacey
2019-11-16 Labels cleaned
2019-11-17 Minor rewiring
    Rewired to remove some vias
2019-11-17 Labeling boxes added
    Boxed the servo stuff and buttons/switch
2019-11-17 Fixed
2019-11-17 n-Mosfet changed direction
    2 hours with a major case of the big dumb
2019-11-17 Wired re-oriented MOSFETs
2019-11-26 Expanded stuff
2019-11-26 Moved servos
2019-11-26 Made spacings between pin heads and wires even
2019-11-26 moved capacitors
2019-11-26 Shield +.5'
2019-11-26 Added shield file
2019-12-12 Removed 2019 material and updated for 2020 in Documentation
2019-12-12 Changed the LED's to 5VL and fixed the wiring for it and added X's
2019-12-13 All but a bit
2019-12-14 Trying to figure out how to make a bom
2019-12-14 Different shield
2019-12-14 Minor changes
2019-12-14 Wires
2019-12-14 Stuff
2019-12-14 Gerbs
2020-01-21 Created Step File
2020-03-04 Rev 2 Anderson Change
2020-03-05 Capacitor move
2020-09-12 created project
2020-10-08 Schematic Completed
2020-10-08 Fixed Heirarchical Boxes
2020-10-09 Replaced zener with schottky
2020-10-13 Fixed MOSFET's
2020-10-14 Fixed Tiva Pin
2020-10-14 Annotated Symbols
2020-10-14 Fixed Switch and Buttons
2020-10-28 fixed bucks
2020-11-15 footprints
2020-11-15 added netlist
2020-11-15 start layout
2020-11-15 layout 2
2020-11-15 layout 3
2020-11-16 layout 4
2020-11-16 layout 5
2020-11-16 layout 6
2020-11-16 layout 7
2020-11-17 layout 8
2020-11-18 layout 9
2020-11-18 layout 10
2020-11-18 layout 11
2020-11-18 layout 12
2020-11-18 layout 13
2020-11-19 layout 14
2020-11-20 layout 15
2020-11-20 layout 16
2020-11-20 layout 17
2020-11-20 layout 18
2020-11-28 layout 19
2020-11-28 checklist
2020-11-30 Moved Gerbs to the Manufacturing Folder
2021-09-28 deleted everything
    Deleted all of last years files
2021-10-02 created file structure, created new kiCAD project
2021-10-02 added Andersons and Buck Converters
2021-10-06 two heiriachical sheets added
    added the molex and switches sheets so we can work on them seperately
2021-10-06 created molex connectors
2021-10-06 swiches sheet
    swithces subsheet with 3 toggle is done
2021-10-06 added tags
    added output tags to the outside of the switch sheet
2021-10-08 added pins, global labels, and hierarchial labels to the molex hierarchial sheet
2021-10-08 fixed h-labels in molex sheet
2021-10-08 made buck converter sheet less ugly
2021-10-08 fixed h-labels in main and molex
2021-10-08 created sheet for 3.3V Buck Converter
2021-10-08 created sheet for 5.5V buck converter
2021-10-08 seperated buck converters sheet into 2 sheets
2021-10-08 added zenner diodes
2021-10-08 made it less ugly
2021-10-08 added servo indicators sheet
2021-10-08 added servo indicator sheet and some connection
2021-10-08 updated labels
2021-10-08 added power indicators
    added power indicator heirachical sheet
2021-10-08 power indicators
    added power indicators
2021-10-08 Added the Teensy
    Added the Teensey and some tags and things. It should be done. or at least ready for review
2021-10-09 connected everything up and changed power to accomodate teensy instead of tiva
2021-10-09 added h-labels
2021-10-10 added text
2021-10-10 added more text
2021-10-10 added labels, numbered everything, added no connection to pins. Still can't get past a couple pf errors in the electrical rules check
2021-10-10 updated labels and file names
2021-10-10 deleted unessecary files and added Title
2021-10-10 sheet has been reviewed
    schematic has been reviewed. and resister values have been changed. as well as a ground being added
2021-10-16 Post PDR changes
2021-10-16 deleted unused files
2021-10-16 deleted more unused files
2021-10-20 added PDF to documentation and deleted notes.txt
2021-10-22 now powering the teensy w 3.3VL instead of 5VL
2021-11-06 added BOM
2021-11-06 BOM update
2021-11-06 footprints added
    some footprints have been added but only a few
2021-11-06 created BOM
2021-11-07 Added more footprints
    I added more footprints. Not done yet. I'd like to come back when when I can verify with max about some of the other components.
2021-11-12 Footprints finished
    the footprints are finished. the RJ45 connector has been added for eithernet.
    the net is in the layout thing but I haven't moved anything yet
2021-11-12 worked on BOM, not complete
2021-11-13 moves ethernet and Molex SL connectors to top, Andersons will also go on top if we are allowed to make the board even wider.
2021-11-18 moved footprints
    I moved some footprints around and asked some questions about trace width. as well as fixed the ethernet cap footprint
2021-11-18 ordered connectors and arranged PWM indicators
2021-11-18 moved the backup molex
    added ground planes, moved backup molex, a few other things.
2021-11-19 Added traces
    I'm not done yet but its pretty close
2021-11-19 basically done
    the switch still isn't connected because the footprint seemed off an I wasn't sure what that was about.
    Buuuut otherwise I think it looks pretty good.
2021-11-19 after review
    some changes needed but yeah
2021-11-22 ethernet fixed.
    the ethernet is fixed. as well as the switch footprint association issue.
    I'm not certain that the current footprint being used matches an actual switch. also this edit does not have the 3x2 microfit connectors
2021-12-02 new connectors and decals
    i have the 3x2 molex on here as well as some cowboy bebop decals.
    the swtich still needs be confirmed.
2021-12-02 bigger swordfish
    bigger swordfish
2021-12-03 the correct switch, and some decals
    some decals and the correct switch
2021-12-03 oops it needed the copper filled again
    filled copper
2021-12-03 3D models
    added some 3D models
2021-12-03 non-copyrighted silks
    non-copyrighted silkscreens are probably a good idea
2021-12-03 oops don't forget to fill copper
    Isaac, always make sure to fill the copper!
2021-12-04 moved the 3x2 connectors down
    moved the 3x2 connectors down and shifted some stuff around so I didn't have to increase the size of the board
2021-12-04 steps and gerbs
    steps and gerbs have been added
2021-12-08 generated gerbs
2021-12-30 deleted autosave file and cache files
2021-12-30 removed redundant libraries
2021-12-30 removed incomplete BOM that was accidentally merged to master
2022-05-19 created rev2 bom
2022-09-14 Gimbal_Board_2022
    Started to move previous designs onto a new schematic. Started to redo the buck converter to only have two andersons as the inputs.
2022-09-14 cleaned up files
2022-09-14 pro files
2022-09-14 Removed broken project file
2022-09-20 Added project file to repo
2022-09-21 schematic review changes
2022-09-26 Changed Manual Switches resistor value to 100 and added global label
2022-09-26 Named Leds and oke to tsr added more leds and 5 v resistor to 300
2022-09-28 Added in 9 and 3 pin, redid some reference label
2022-09-30 Merged Grounds Changed Leds
    Merged Grounds on the Teensy
    Changed Servo control LEDs to yellow
2022-09-30 Redid labels, Edited Teensy ground, changed leds
    Redid labels on LEDs
    Changed LEDs on manual servo switch to yellow
    Edited and decompressed ground on Teensy
    Also removed the 8 label on Teensy and changed output to an x
    General cleaning as well
2022-09-30 Checking save
2022-09-30 Rearranged and cleaned up
    Cleaned up Loose ends on circuits
    Rearranged some
2022-09-30 Formatting
2022-09-30 changed 3v back to oki and added in capacitors, deleted servo 8 tag from teensy
2022-09-30 changed sheet size
2022-10-01 organized schematic and changed yellow to blue and blue to yellow for LED
2022-10-01 Reassigned labels
2022-10-01 Added PDF
    Followed steps from discord
2022-10-04 Labeled Ethernet
    1TX+
    2TX-
    3GND
    4LED
    5RX-
    6RX+
2022-10-04 Electrical Check Fix
    Fixed Some lables
2022-10-12 Added in PCB and started organizing
2022-10-18 Wire management
2022-10-18 Ran an electrical rule check
2022-10-19 Rearranged and rerouted connections
2022-10-23 Cable management
    Redid ethernet lines to make them closer in length to each other
    Ran 3.3 line around bottom
2022-10-24 Connected leds for servos
    Connected leds for servos
2022-10-24 Cable management, added edge cuts, and resized ground planes
2022-10-26 Rearranged components
    delete trace
    made board more compact
    labeled
2022-10-26 Footprint assignment for capacitors
2022-10-26 Started servo port 5v
2022-10-31 Named some switches and added in volt line
2022-10-31 wiring
2022-11-01 Completed wiring and changed position of various pins
2022-11-01 added signature
2022-11-03 Rewired trace and labeled diodes
2022-11-03 rewired 3.3 v line to the switches and redrew edgecuts
2022-11-03 moved some names around
2022-11-03 Redid header
2022-11-03 redrew edgecuts and finished board
2022-11-11 Updated PDF for Schematic
